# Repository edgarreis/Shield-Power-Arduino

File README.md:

# Shield-Power-Arduino
Shield de Potência com Relés e Triacs para o Arduino UNO

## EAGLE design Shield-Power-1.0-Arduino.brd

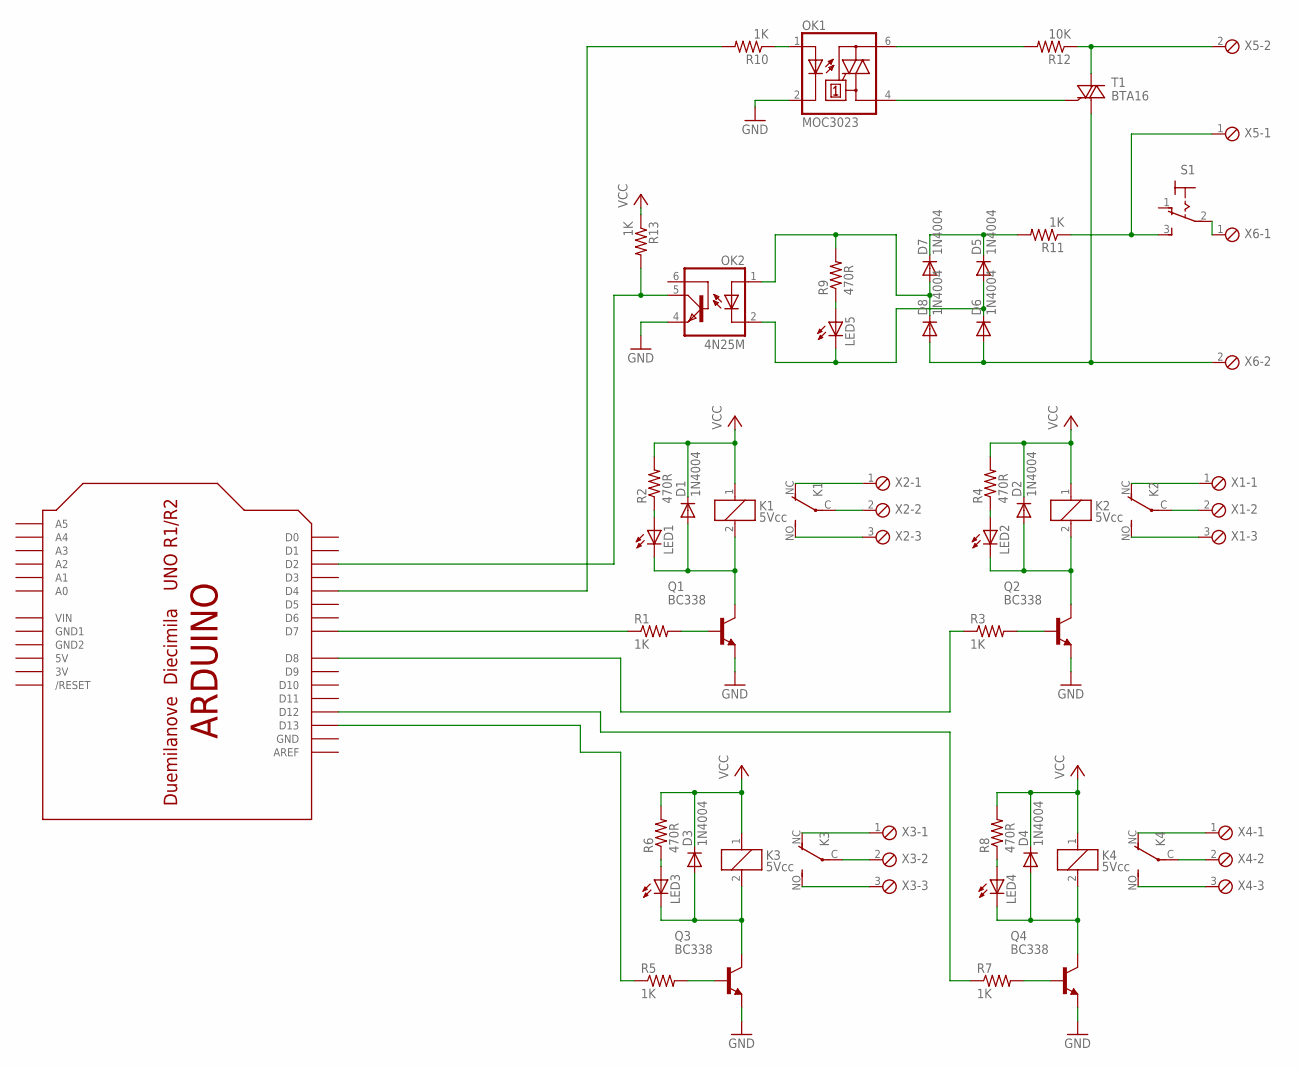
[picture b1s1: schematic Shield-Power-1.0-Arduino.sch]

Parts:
D1, D2, D3, D4, D5, D6, D7, D8: 1N4004; DO41-10
K1, K2, K3, K4: 5Vcc; CQ1
LED1, LED2, LED3, LED4, LED5: LED3MM
OK1: MOC3023; DIL06B
OK2: 4N25M; DIL06
Q1, Q2, Q3, Q4: BC338; TO92-EBC
R1, R3, R5, R7, R10, R11, R13: 1K; 0207/10
R2, R4, R6, R8, R9: 470R; 0207/10
R12: 10K; 0207/10
S1: 320-916
T1: BTA16; TO220BV
U$1: ARDUINO-NOHOLE
X1, X2, X3, X4: MPT3; 3POL254
X5, X6: MPT2; 2POL254

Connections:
3V: U$1.3V
5V: U$1.5V
GND: OK1.2 (C), OK2.4 (EMI), Q1.E, Q2.E, Q3.E, Q4.E, U$1.GND
GND1: U$1.GND1
GND2: U$1.GND2
unnamed: K2.C, X1.2
unnamed: K2.NC (O), X1.1
unnamed: K1.C, X2.2
unnamed: K1.NC (O), X2.1
unnamed: K1.NO (S), X2.3
unnamed: K2.NO (S), X1.3
unnamed: Q2.B, R3.2
unnamed: LED2.A, R4.1
unnamed: D2.A, K2.2, LED2.K (C), Q2.C
unnamed: K3.C, X3.2
unnamed: K3.NC (O), X3.1
unnamed: K3.NO (S), X3.3
unnamed: Q1.B, R1.2
unnamed: LED1.A, R2.1
unnamed: Q3.B, R5.2
unnamed: D1.A, K1.2, LED1.K (C), Q1.C
unnamed: LED3.A, R6.1
unnamed: D3.A, K3.2, LED3.K (C), Q3.C
unnamed: K4.C, X4.2
unnamed: K4.NC (O), X4.1
unnamed: K4.NO (S), X4.3
unnamed: Q4.B, R7.2
unnamed: LED4.A, R8.1
unnamed: D4.A, K4.2, LED4.K (C), Q4.C
unnamed: R1.1, U$1.D7
unnamed: OK1.1 (A), R10.1
unnamed: R3.1, U$1.D8
unnamed: R5.1, U$1.D13
unnamed: R7.1, U$1.D12
unnamed: OK1.6 (A2), R12.2
unnamed: LED5.A, R9.1
unnamed: D6.A, D8.A, T1.T1 (A1), X6.2
unnamed: S1.2, X6.1
unnamed: OK1.4 (A1), T1.G
unnamed: R11.1, S1.3 (S), X5.1
unnamed: D5.C, D7.C, R11.2
unnamed: D5.A, D6.C, LED5.K (C), OK2.2 (C)
unnamed: OK2.5 (COL), R13.2, U$1.D2
unnamed: R10.2, U$1.D4
unnamed: R12.1, T1.T2 (A2), X5.2
VCC: D1.C, D2.C, D3.C, D4.C, K1.1, K2.1, K3.1, K4.1, R2.2, R4.2, R6.2, R8.2, R13.1
VCC1: D7.A, D8.C, OK2.1 (A), R9.2
VIN: U$1.VIN

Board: 2 copper layers, 45 parts (0 on the bottom side), 43 nets, no tracks yet.

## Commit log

2016-04-28 Added files via upload
